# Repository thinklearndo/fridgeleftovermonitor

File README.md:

# fridgeleftovermonitor
A project to show using the Holtek HT68F001 as a timer. Useful for keeping nasty leftovers out of your fridge.

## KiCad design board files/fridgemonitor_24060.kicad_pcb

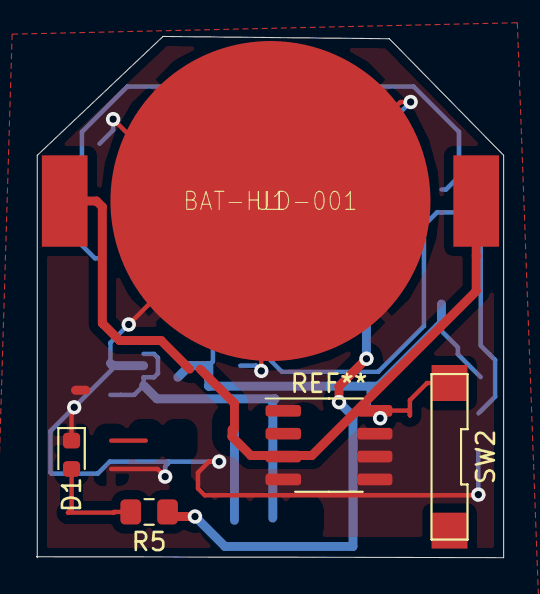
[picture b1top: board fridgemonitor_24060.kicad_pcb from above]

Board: 2 copper layers, 26.0 x 29.0 mm, 4 parts (0 on the bottom side), 3 nets.

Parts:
D1: LED; LED_0603_1608Metric
R5: R; R_0805_2012Metric_Pad1.15x1.40mm_HandSolder
SW2: SW_Push; PTS636-SK50-LFS
U1: BAT-HLD-001

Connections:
+3V3: U1.+@1, U1.+@2
GND: D1.1, U1.-
unnamed: D1.2, R5.2

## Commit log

2022-04-28 adding board files and a pic, still need to get my code
2022-05-07 added poorly documented assembly files...
